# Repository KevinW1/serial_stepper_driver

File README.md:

# serial_stepper_driver
Simple stepper motor driver that can be controlled via serial communication.

Most existing drivers I found did not support 3 switch or analog inputs, so I created this.

Mouser parts:
https://www.mouser.com/ProjectManager/ProjectDetail.aspx?AccessID=6cd5e76669

Micro:
https://www.pjrc.com/store/teensy40.html

Driver:
https://www.pololu.com/product/3768

|  |  |  |
|-----------|-----------|------------|

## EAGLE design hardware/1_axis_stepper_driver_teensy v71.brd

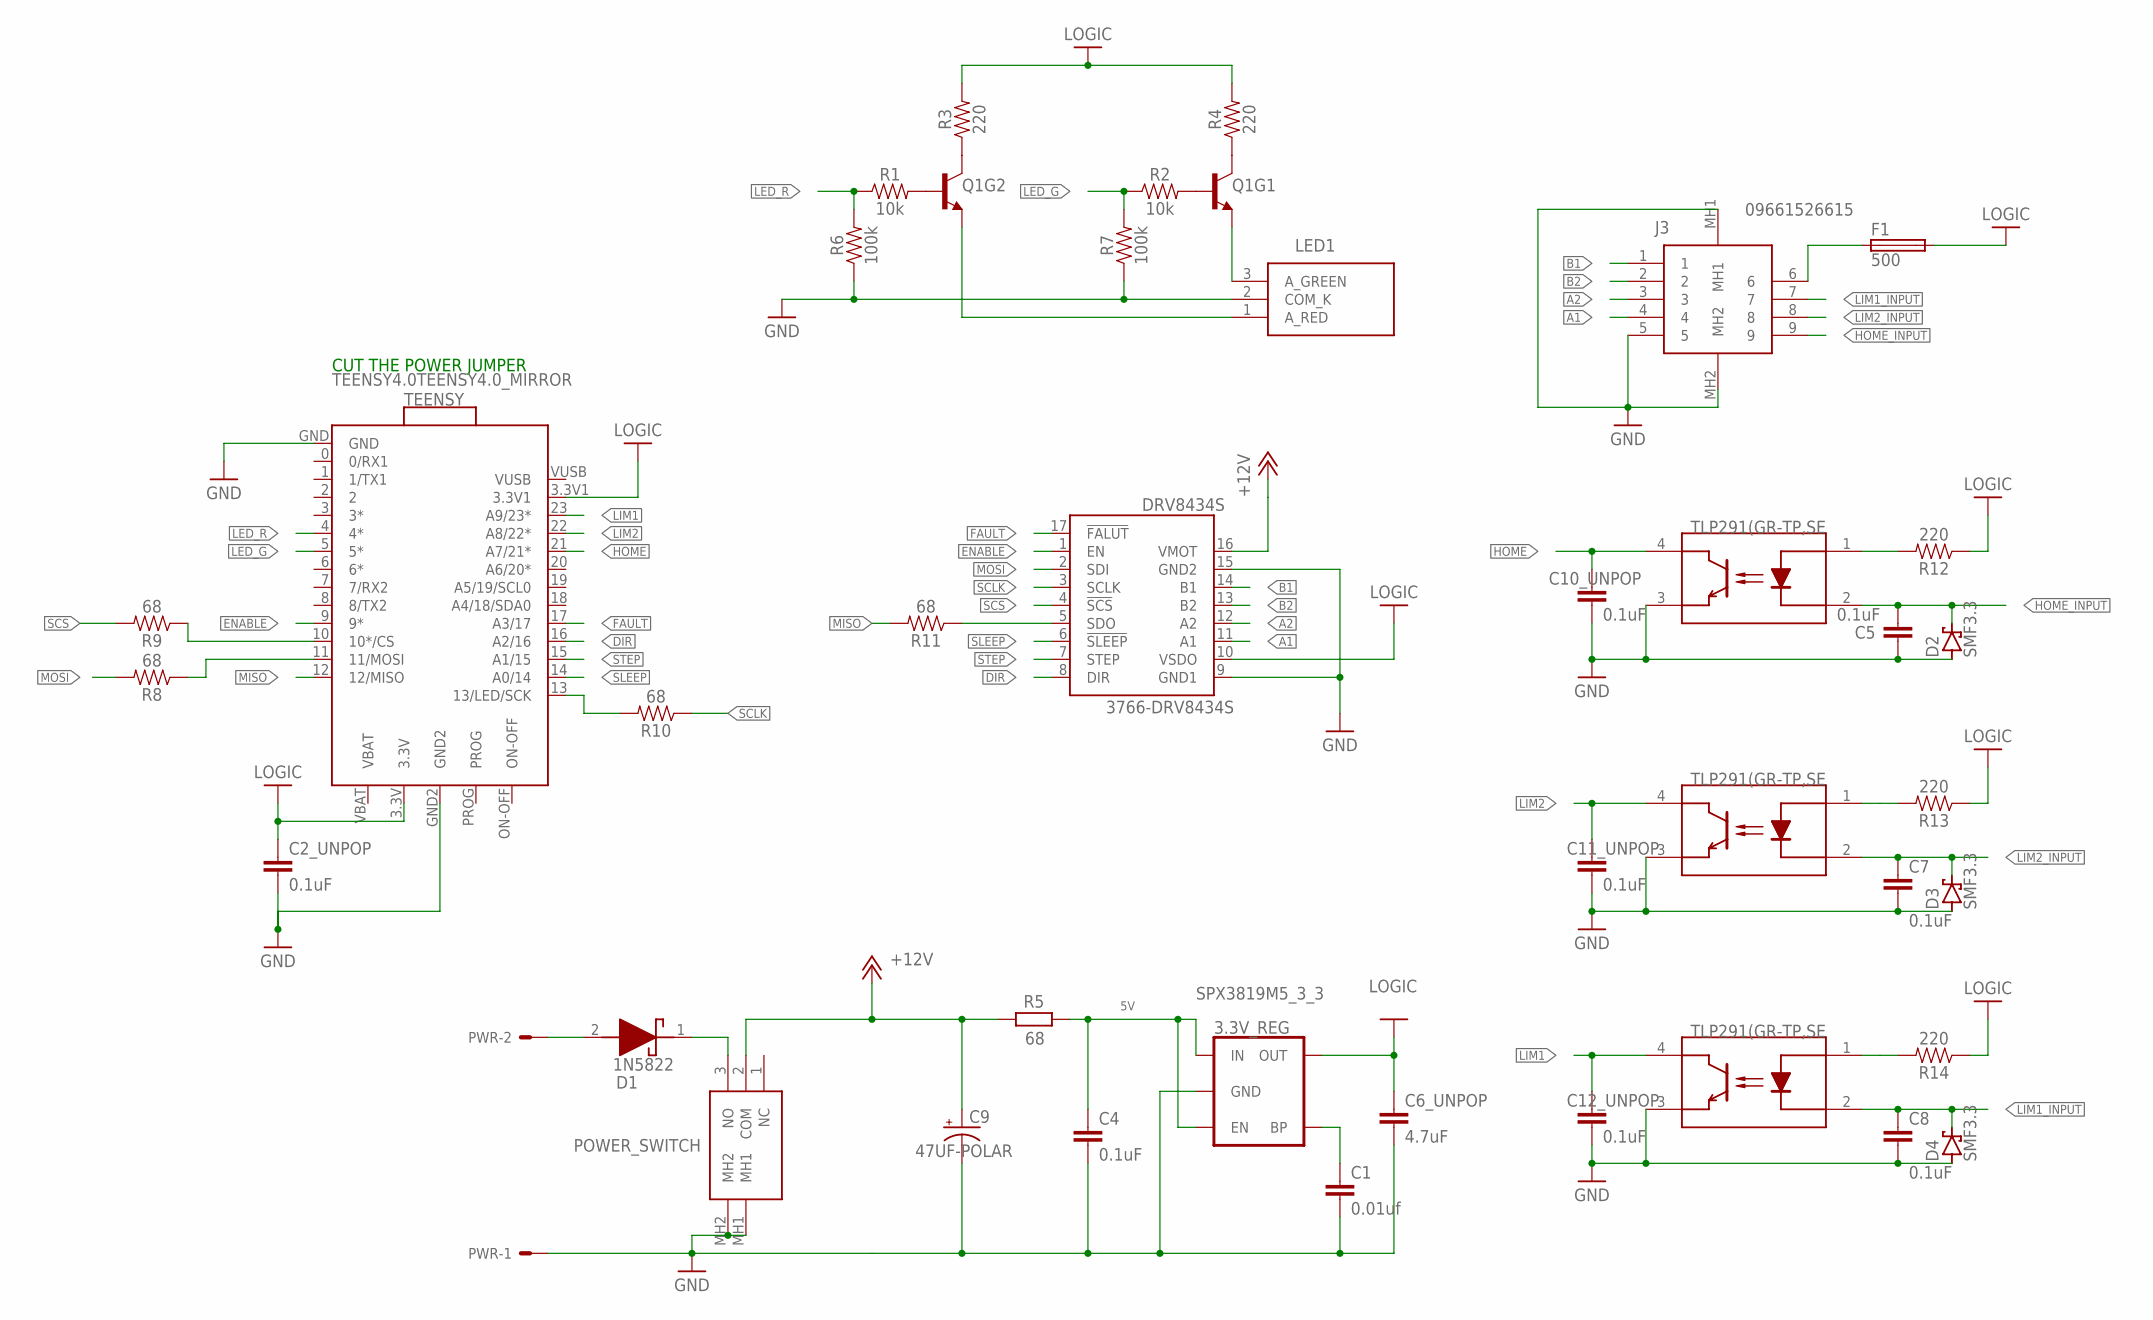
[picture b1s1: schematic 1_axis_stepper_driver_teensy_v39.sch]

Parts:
3.3V_REG: SPX3819M5_3_3; SOT23-5
C1: 0.01uf; 0603
C2_UNPOP, C4, C5, C7, C8, C10_UNPOP, C11_UNPOP, C12_UNPOP: 0.1uF; 0603
C6_UNPOP: 4.7uF; 0603
C9: 47UF-POLAR; PANASONIC_D
D1: 1N5822; DIOAD3070W130L950D530
D2, D3, D4: SMF3.3; SOD123FL
DRV8434S: 3766-DRV8434S; DRV8434S
F1: 500; FUSC1608X60N
J3: 09661526615
LED1: WP42WUM_EGW; WP42WUMEGW
POWER_SWITCH: 200MSP1T2B2M6RE
PWR: 22-27-2021-02; 6410-02
Q1: TRANS_NPN_DUAL-MBT3904DW1T1; SC70-6
R1, R2: 10k; 0603
R3, R4, R12, R13, R14: 220; 0603
R5: 68; RESC6332X71
R6, R7: 100k; 0603
R8, R9, R10, R11: 68; 0603
TEENSY: TEENSY4.0TEENSY4.0_MIRROR; TEENSY4.0_MIRROR
U1, U2, U3: TLP291(GR-TP,SE

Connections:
5V: 3.3V_REG.1 (IN), 3.3V_REG.3 (EN), C4.1, R5.2
+12V: C9.+, DRV8434S.16 (VMOT), POWER_SWITCH.2 (COM), R5.1
A1: DRV8434S.11 (A1), J3.4
A2: DRV8434S.12 (A2), J3.3
B1: DRV8434S.14 (B1), J3.1
B2: DRV8434S.13 (B2), J3.2
DCIN: D1.2 (A), PWR.2
DCSAFE: D1.1 (K), POWER_SWITCH.3 (NO)
DIR: DRV8434S.8 (DIR), TEENSY.16 (A2/16)
ENABLE: DRV8434S.1 (EN), TEENSY.9 (9*)
FAULT: DRV8434S.17 (!FALUT), TEENSY.17 (A3/17)
GND: 3.3V_REG.2 (GND), C1.2, C2_UNPOP.2, C4.2, C5.2, C6_UNPOP.2, C7.2, C8.2, C9.-, C10_UNPOP.2, C11_UNPOP.2, C12_UNPOP.2, D2.A, D3.A, D4.A, DRV8434S.9 (GND1), DRV8434S.15 (GND2), J3.5, J3.MH1, J3.MH2, LED1.2 (COM_K), POWER_SWITCH.MH1, POWER_SWITCH.MH2, PWR.1, R6.1, R7.1, TEENSY.GND, TEENSY.GND2, U1.3 (EMITTER), U2.3 (EMITTER), U3.3 (EMITTER)
HOME: C10_UNPOP.1, TEENSY.21 (A7/21*), U1.4 (COLLECTOR)
HOME_INPUT: C5.1, D2.C, J3.9, U1.2 (CATHODE)
LED_G: R2.1, R7.2, TEENSY.5 (5*)
LED_R: R1.1, R6.2, TEENSY.4 (4*)
LIM1: C12_UNPOP.1, TEENSY.23 (A9/23*), U3.4 (COLLECTOR)
LIM1_INPUT: C8.1, D4.C, J3.7, U3.2 (CATHODE)
LIM2: C11_UNPOP.1, TEENSY.22 (A8/22*), U2.4 (COLLECTOR)
LIM2_INPUT: C7.1, D3.C, J3.8, U2.2 (CATHODE)
LOGIC: 3.3V_REG.5 (OUT), C2_UNPOP.1, C6_UNPOP.1, DRV8434S.10 (VSDO), F1.2, R3.2, R4.2, R12.1, R13.1, R14.1, TEENSY.3.3V, TEENSY.3.3V1
MISO: R11.2, TEENSY.12 (12/MISO)
MOSI: DRV8434S.2 (SDI), R8.2
unnamed: Q1.6 (C), R3.1
unnamed: LED1.1 (A_RED), Q1.1 (E)
unnamed: Q1.2 (B), R1.2
unnamed: Q1.5 (B), R2.2
unnamed: Q1.3 (C), R4.1
unnamed: LED1.3 (A_GREEN), Q1.4 (E)
unnamed: F1.1, J3.6
unnamed: 3.3V_REG.4 (BP), C1.1
unnamed: R8.1, TEENSY.11 (11/MOSI)
unnamed: R9.1, TEENSY.10 (10*/CS)
unnamed: R10.2, TEENSY.13 (13/LED/SCK)
unnamed: DRV8434S.5 (SDO), R11.1
unnamed: R12.2, U1.1 (ANODE)
unnamed: R13.2, U2.1 (ANODE)
unnamed: R14.2, U3.1 (ANODE)
SCLK: DRV8434S.3 (SCLK), R10.1
SCS: DRV8434S.4 (!SCS), R9.2
SLEEP: DRV8434S.6 (!SLEEP), TEENSY.14 (A0/14)
STEP: DRV8434S.7 (STEP), TEENSY.15 (A1/15)
VBAT: TEENSY.VBAT
VUSB: TEENSY.VUSB

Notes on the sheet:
CUT THE POWER JUMPER

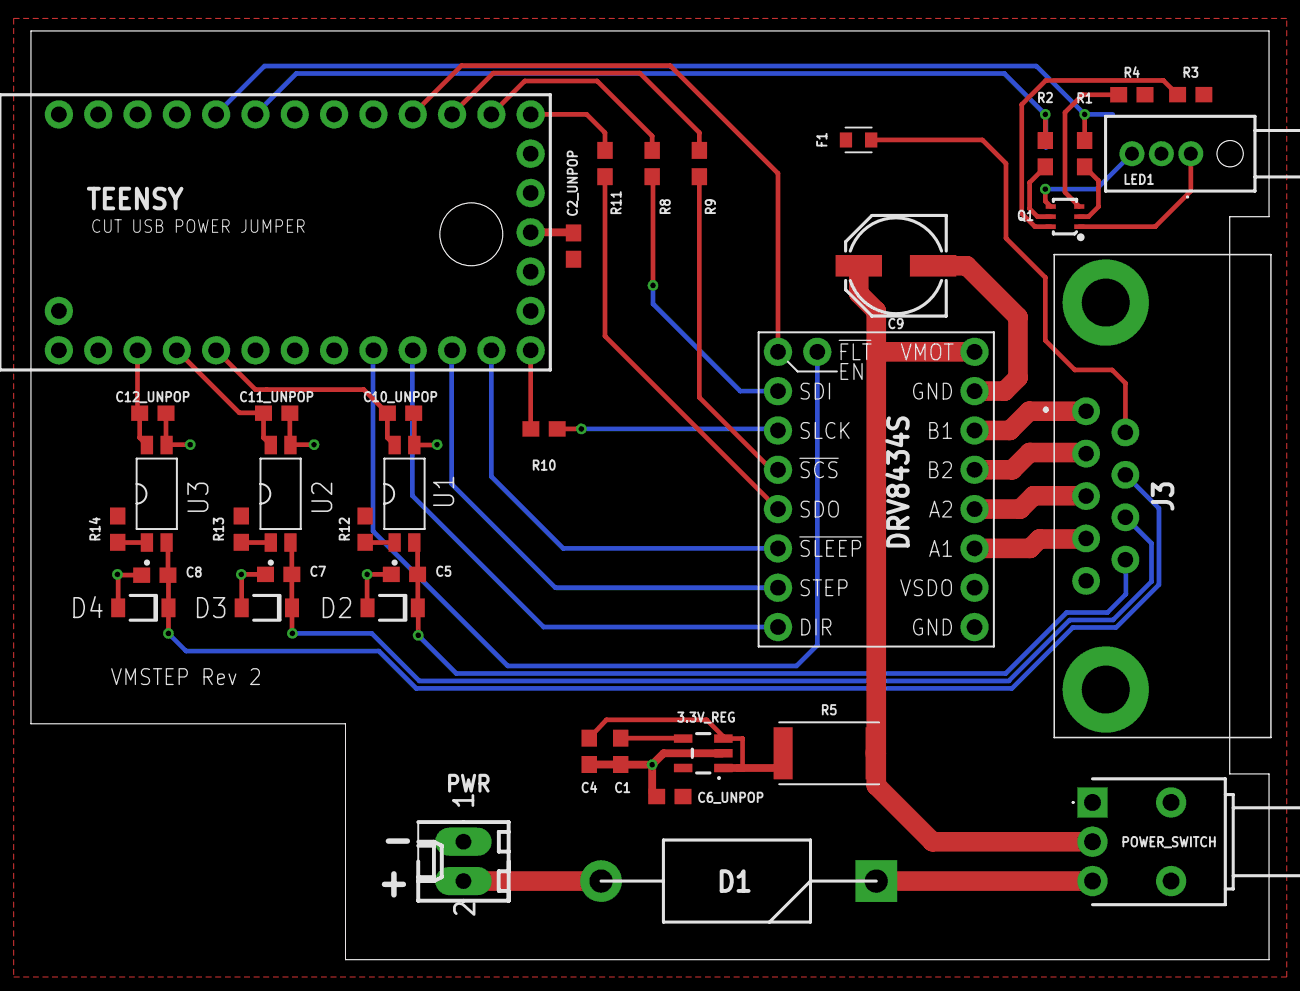
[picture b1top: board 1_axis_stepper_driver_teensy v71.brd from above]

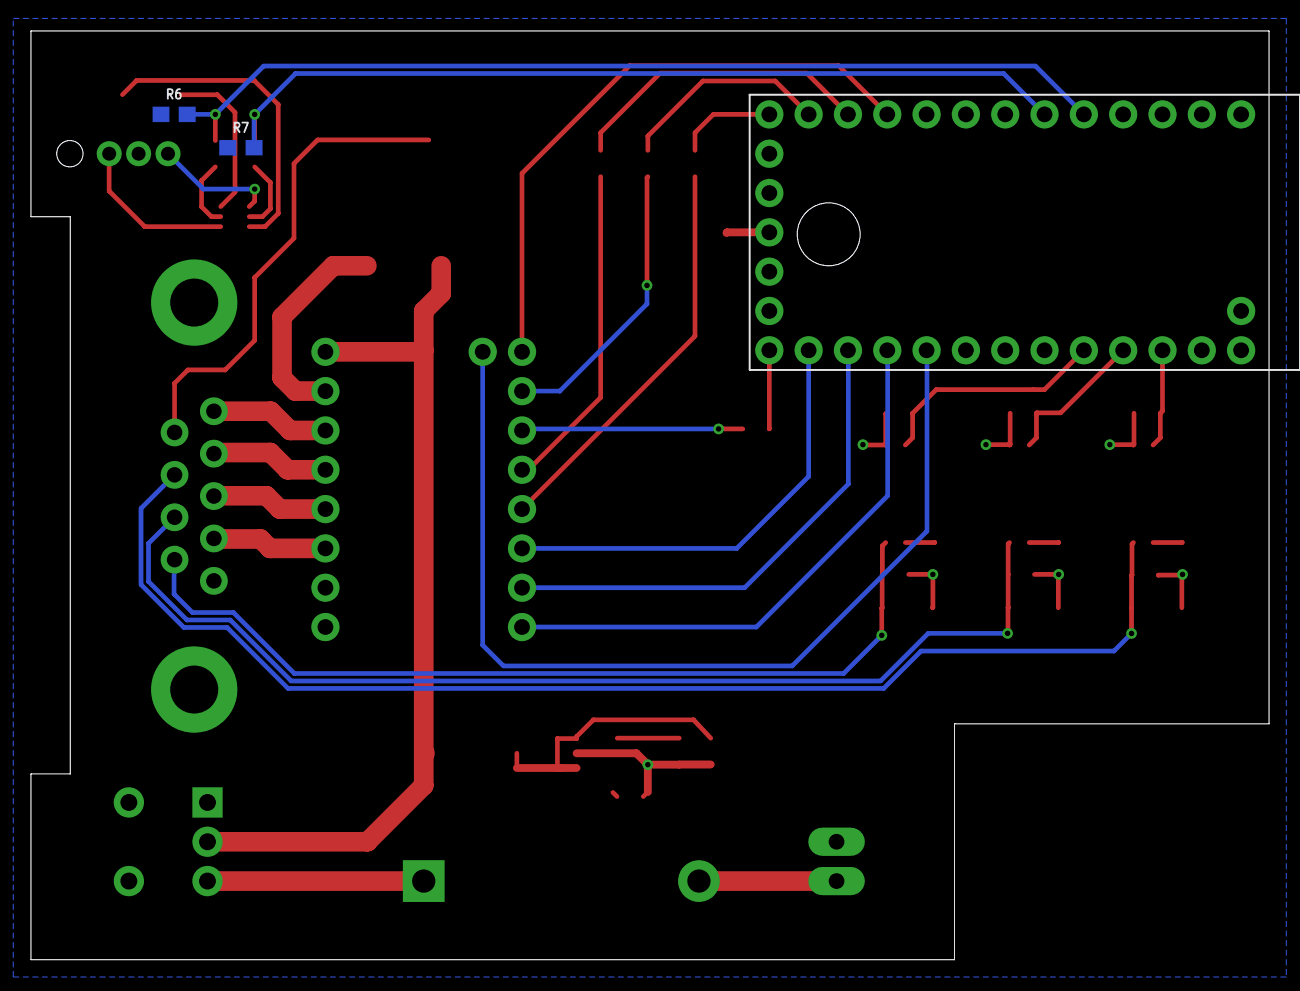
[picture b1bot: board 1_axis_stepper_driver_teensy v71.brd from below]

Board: 2 copper layers, 80.0 x 60.0 mm, 41 parts (2 on the bottom side), 42 nets.

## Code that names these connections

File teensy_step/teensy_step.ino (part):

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static constexpr byte PIN_STEP = 7;
static constexpr byte PIN_DIR = 8;
static constexpr byte PIN_ENABLE = 9;
static constexpr byte PIN_SCS = 10;
static constexpr byte PIN_FAULT = 17;
// system
static constexpr byte PIN_LED_R = 4;
static constexpr byte PIN_LED_G = 5;
// Sensors
static constexpr byte PIN_LIM1 = 16;
static constexpr byte PIN_LIM2 = 15;
static constexpr byte PIN_HOME = 14;
// system control
static constexpr uint16_t LED_PULSE_PERIOD = 2000;  // 2 second cycle

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Mode device_mode = Mode::idle;
unsigned long idle_time = 0;
SerialTransciever Comms;
Motor motor(PIN_SCS, PIN_STEP, PIN_DIR, PIN_ENABLE, PIN_SLEEP, settings);

void setup() {
    reset_controller();
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        return;
    }
    // sensors
    pinMode(PIN_LIM1, INPUT_PULLUP);
    pinMode(PIN_LIM2, INPUT_PULLUP);
    pinMode(PIN_HOME, INPUT_PULLUP);
    // driver
    pinMode(PIN_FAULT, INPUT_PULLUP);  // logic low = fault
    // led
    pinMode(PIN_LED_R, OUTPUT);
    pinMode(PIN_LED_G, OUTPUT);

    init_serial(19200);
    motor.init();
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void enter_idle_state() {
    device_mode = Mode::idle;
    idle_time = millis();
    analogWrite(PIN_LED_G, 128);
    analogWrite(PIN_LED_R, 0);
}

void enter_sleep_state() {
    device_mode = Mode::sleep;
    // apply sleep current to motor
    motor.set_current(settings.data.sleep_current);
    analogWrite(PIN_LED_R, 0);
    analogWrite(PIN_LED_G, 128);
}

void enter_moving_state() {
    device_mode = Mode::moving;
    // apply run current to motor
    motor.set_current(settings.data.step_current);
    analogWrite(PIN_LED_G, 255);
    analogWrite(PIN_LED_R, 0);
}

void enter_homing_state() {
    device_mode = Mode::homing;
    // apply run current to motor
    motor.set_current(settings.data.step_current);
    analogWrite(PIN_LED_G, 128);
    analogWrite(PIN_LED_R, 128);
}

void enter_fault_state() {
    device_mode = Mode::fault;
    motor_hard_stop();
    motor.disable_driver();
    analogWrite(PIN_LED_G, 0);
    analogWrite(PIN_LED_R, 255);
}

void motor_goto(byte data[]) {
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
    // check home
    if (settings.data.enable_home && device_mode == Mode::homing) {
        if (digitalRead(PIN_HOME) == settings.data.home_sig_polarity) {
            enter_idle_state();
            motor.reset_position();
            Comms.send(REPLY_DONE);
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    }
    // check lim 1
    if (settings.data.enable_lim1) {
        if (digitalRead(PIN_LIM1) == settings.data.lim1_sig_polarity) {
            enter_fault_state();
            Comms.send(REPLY_FAULT, FAULT_LIMT1);
        }
    }
    // check lim 2
    if (settings.data.enable_lim2) {
        if (digitalRead(PIN_LIM2) == settings.data.lim2_sig_polarity) {
            enter_fault_state();
            Comms.send(REPLY_FAULT, FAULT_LIMT2);
        }
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    // pulse led geen
    float phase = (float)((millis() % LED_PULSE_PERIOD) * 2 * PI) / LED_PULSE_PERIOD;
    byte brightness = (byte)(128 + 127 * sin(phase));
    analogWrite(PIN_LED_G, brightness);
}

void loop() {
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
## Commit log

2024-10-20 Settings hook now working
2024-10-20 hook up accel
2024-10-21 Add motor stop command
2024-11-28 Add settings range checks
2024-11-30 Not working, homes too quickly and faults on startup sometimes
2024-12-18 working, needs cleanup
2024-12-19 Improved homing using accel
2024-12-20 Add enable/disable commands
2024-12-22 Add new commands
2024-12-22 Driver fault handling
2024-12-23 cleanup
2024-12-23 rename to vmstep
2024-12-23 Clean up python examples
2024-12-24 use bitfileds for settings
2024-12-24 Refactored Serial comms into state machine and handled a few extra error cases
2024-12-25 Brendan refactor
2024-12-27 Fix microsteps, remove settings.cpp
2024-12-27 Improve typing in python strict
2025-01-24 Simplify firmware and version reporting
2025-01-25 Update pins for new hardware
2025-01-30 Add hardware files
2025-01-30 Add Gerber files
2025-03-12 Zero motor before homing to prevent overflow

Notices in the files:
parts and their libraries:
SparkFun-Boards: Licensing: Creative Commons ShareAlike 4.0 International - https://creativecommons.org/licenses/by-sa/4.0
